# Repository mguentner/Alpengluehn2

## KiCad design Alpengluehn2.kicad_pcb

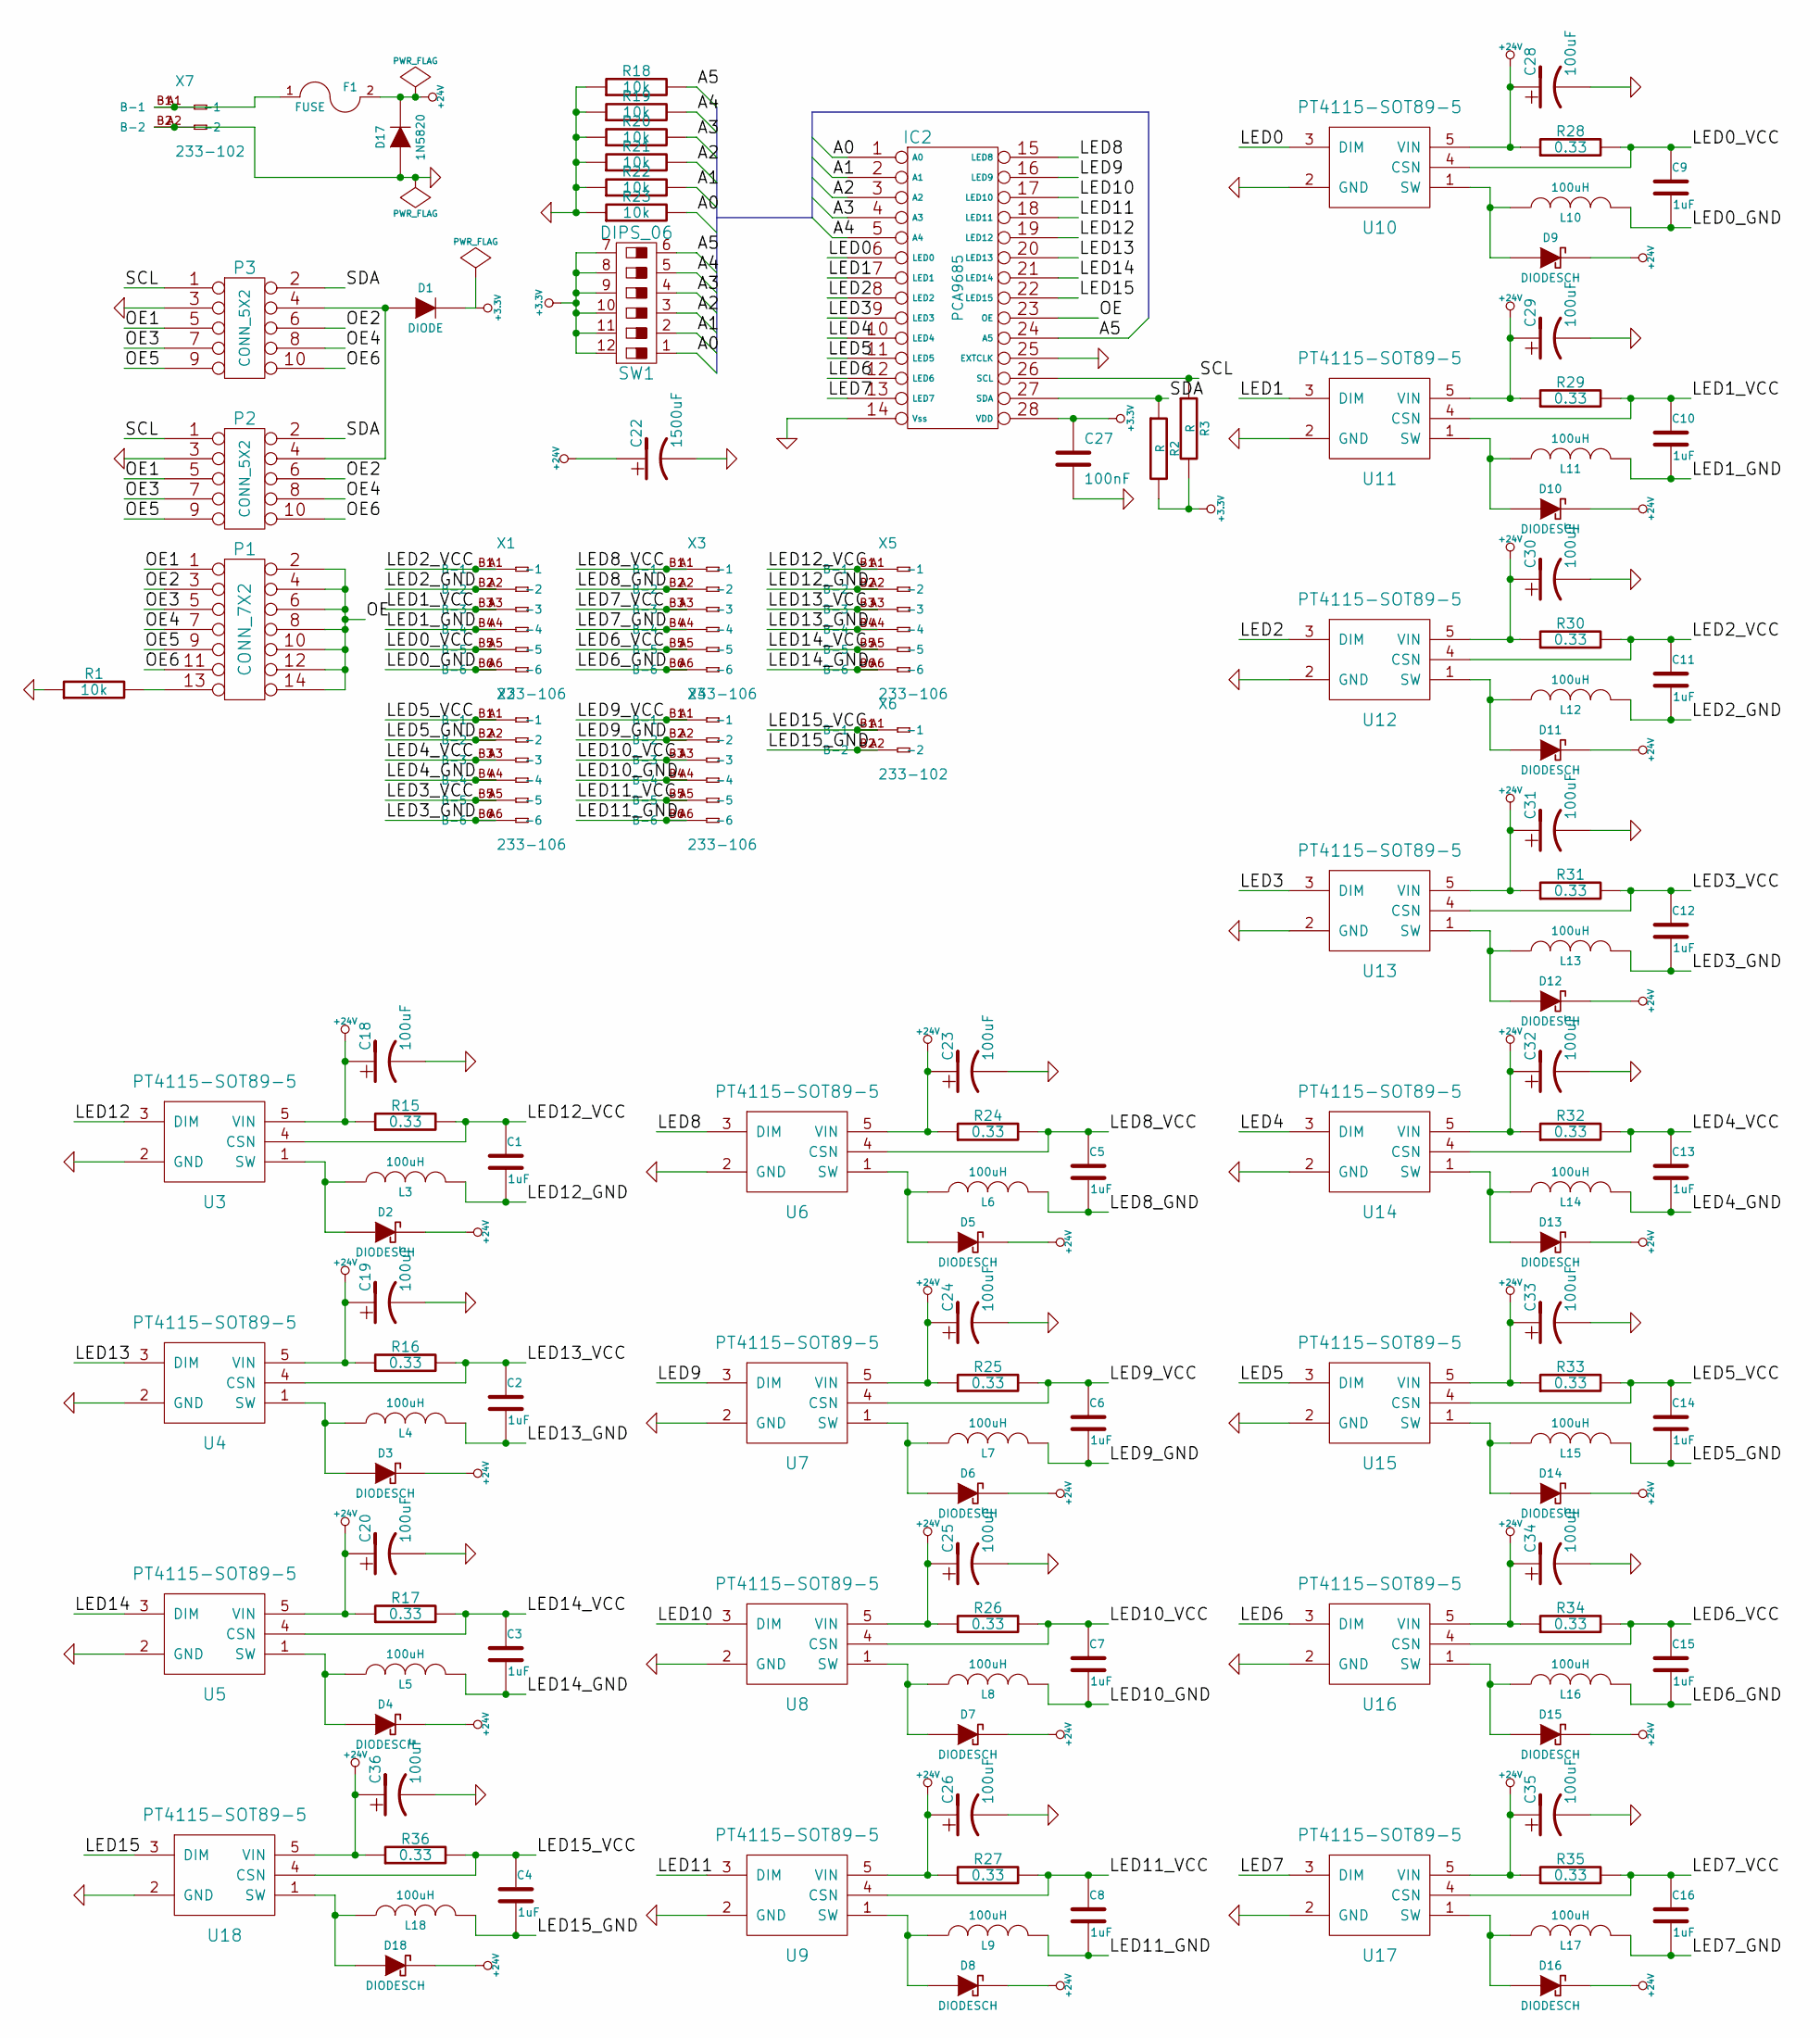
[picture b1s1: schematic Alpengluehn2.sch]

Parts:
C1, C2, C3, C4, C5, C6, C7, C8, C9, C10, C11, C12, C13, C14, C15, C16: 1uF
C18, C19, C20, C23, C24, C25, C26, C28, C29, C30, C31, C32, C33, C34, C35, C36: 100uF
C22: 1500uF
C27: 100nF
D1: DIODE
D2, D3, D4, D5, D6, D7, D8, D9, D10, D11, D12, D13, D14, D15, D16, D18: DIODESCH
D17: 1N5820
F1: FUSE
IC2: PCA9685
L3, L4, L5, L6, L7, L8, L9, L10, L11, L12, L13, L14, L15, L16, L17, L18: 100uH
P1: CONN_7X2
P2, P3: CONN_5X2
R1, R18, R19, R20, R21, R22, R23: 10k
R2, R3: R
R15, R16, R17, R24, R25, R26, R27, R28, R29, R30, R31, R32, R33, R34, R35, R36: 0.33
SW1: DIPS_06
U3, U4, U5, U6, U7, U8, U9, U10, U11, U12, U13, U14, U15, U16, U17, U18: PT4115-SOT89-5
X1, X2, X3, X4, X5: 233-106; con-wago-233-106
X6, X7: 233-102; con-wago-233-102

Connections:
+3.3V: C27.1, D1.2 (K), IC2.28 (VDD), R2.2, R3.2, SW1.7, SW1.8, SW1.9, SW1.10, SW1.11, SW1.12
+24V: C18.1, C19.1, C20.1, C22.1, C23.1, C24.1, C25.1, C26.1, C28.1, C29.1, C30.1, C31.1, C32.1, C33.1, C34.1, C35.1, C36.1, D2.2 (K), D3.2 (K), D4.2 (K), D5.2 (K), D6.2 (K), D7.2 (K), D8.2 (K), D9.2 (K), D10.2 (K), D11.2 (K), D12.2 (K), D13.2 (K), D14.2 (K), D15.2 (K), D16.2 (K), D17.2 (K), D18.2 (K), F1.2, R15.1, R16.1, R17.1, R24.1, R25.1, R26.1, R27.1, R28.1, R29.1, R30.1, R31.1, R32.1, R33.1, R34.1, R35.1, R36.1, U3.5 (VIN), U4.5 (VIN), U5.5 (VIN), U6.5 (VIN), U7.5 (VIN), U8.5 (VIN), U9.5 (VIN), U10.5 (VIN), U11.5 (VIN), U12.5 (VIN), U13.5 (VIN), U14.5 (VIN), U15.5 (VIN), U16.5 (VIN), U17.5 (VIN), U18.5 (VIN)
/A0: IC2.1 (A0), R23.2, SW1.1
/A1: IC2.2 (A1), R22.2, SW1.2
/A2: IC2.3 (A2), R21.2, SW1.3
/A3: IC2.4 (A3), R20.2, SW1.4
/A4: IC2.5 (A4), R19.2, SW1.5
/A5: IC2.24 (A5), R18.2, SW1.6
/LED0: IC2.6 (LED0), U10.3 (DIM)
/LED0_GND: C9.2, L10.2, X1.A6 (-6), X1.B6 (B-6)
/LED0_VCC: C9.1, R28.2, U10.4 (CSN), X1.A5 (-5), X1.B5 (B-5)
/LED1: IC2.7 (LED1), U11.3 (DIM)
/LED1_GND: C10.2, L11.2, X1.A4 (-4), X1.B4 (B-4)
/LED1_VCC: C10.1, R29.2, U11.4 (CSN), X1.A3 (-3), X1.B3 (B-3)
/LED2: IC2.8 (LED2), U12.3 (DIM)
/LED2_GND: C11.2, L12.2, X1.A2 (-2), X1.B2 (B-2)
/LED2_VCC: C11.1, R30.2, U12.4 (CSN), X1.A1 (-1), X1.B1 (B-1)
/LED3: IC2.9 (LED3), U13.3 (DIM)
/LED3_GND: C12.2, L13.2, X2.A6 (-6), X2.B6 (B-6)
/LED3_VCC: C12.1, R31.2, U13.4 (CSN), X2.A5 (-5), X2.B5 (B-5)
/LED4: IC2.10 (LED4), U14.3 (DIM)
/LED4_GND: C13.2, L14.2, X2.A4 (-4), X2.B4 (B-4)
/LED4_VCC: C13.1, R32.2, U14.4 (CSN), X2.A3 (-3), X2.B3 (B-3)
/LED5: IC2.11 (LED5), U15.3 (DIM)
/LED5_GND: C14.2, L15.2, X2.A2 (-2), X2.B2 (B-2)
/LED5_VCC: C14.1, R33.2, U15.4 (CSN), X2.A1 (-1), X2.B1 (B-1)
/LED6: IC2.12 (LED6), U16.3 (DIM)
/LED6_GND: C15.2, L16.2, X3.A6 (-6), X3.B6 (B-6)
/LED6_VCC: C15.1, R34.2, U16.4 (CSN), X3.A5 (-5), X3.B5 (B-5)
/LED7: IC2.13 (LED7), U17.3 (DIM)
/LED7_GND: C16.2, L17.2, X3.A4 (-4), X3.B4 (B-4)
/LED7_VCC: C16.1, R35.2, U17.4 (CSN), X3.A3 (-3), X3.B3 (B-3)
/LED8: IC2.15 (LED8), U6.3 (DIM)
/LED8_GND: C5.2, L6.2, X3.A2 (-2), X3.B2 (B-2)
/LED8_VCC: C5.1, R24.2, U6.4 (CSN), X3.A1 (-1), X3.B1 (B-1)
/LED9: IC2.16 (LED9), U7.3 (DIM)
/LED9_GND: C6.2, L7.2, X4.A2 (-2), X4.B2 (B-2)
/LED9_VCC: C6.1, R25.2, U7.4 (CSN), X4.A1 (-1), X4.B1 (B-1)
/LED10: IC2.17 (LED10), U8.3 (DIM)
/LED10_GND: C7.2, L8.2, X4.A4 (-4), X4.B4 (B-4)
/LED10_VCC: C7.1, R26.2, U8.4 (CSN), X4.A3 (-3), X4.B3 (B-3)
/LED11: IC2.18 (LED11), U9.3 (DIM)
/LED11_GND: C8.2, L9.2, X4.A6 (-6), X4.B6 (B-6)
/LED11_VCC: C8.1, R27.2, U9.4 (CSN), X4.A5 (-5), X4.B5 (B-5)
/LED12: IC2.19 (LED12), U3.3 (DIM)
/LED12_GND: C1.2, L3.2, X5.A2 (-2), X5.B2 (B-2)
/LED12_VCC: C1.1, R15.2, U3.4 (CSN), X5.A1 (-1), X5.B1 (B-1)
/LED13: IC2.20 (LED13), U4.3 (DIM)
/LED13_GND: C2.2, L4.2, X5.A4 (-4), X5.B4 (B-4)
/LED13_VCC: C2.1, R16.2, U4.4 (CSN), X5.A3 (-3), X5.B3 (B-3)
/LED14: IC2.21 (LED14), U5.3 (DIM)
/LED14_GND: C3.2, L5.2, X5.A6 (-6), X5.B6 (B-6)
/LED14_VCC: C3.1, R17.2, U5.4 (CSN), X5.A5 (-5), X5.B5 (B-5)
/LED15: IC2.22 (LED15), U18.3 (DIM)
/LED15_GND: C4.2, L18.2, X6.A2 (-2), X6.B2 (B-2)
/LED15_VCC: C4.1, R36.2, U18.4 (CSN), X6.A1 (-1), X6.B1 (B-1)
/OE: IC2.23 (OE), P1.2, P1.4, P1.6, P1.8, P1.10, P1.12, P1.14
/OE1: P1.1, P2.5, P3.5
/OE2: P1.3, P2.6, P3.6
/OE3: P1.5, P2.7, P3.7
/OE4: P1.7, P2.8, P3.8
/OE5: P1.9, P2.9, P3.9
/OE6: P1.11, P2.10, P3.10
/SCL: IC2.26 (SCL), P2.1, P3.1, R3.1
/SDA: IC2.27 (SDA), P2.2, P3.2, R2.1
GND: C18.2, C19.2, C20.2, C22.2, C23.2, C24.2, C25.2, C26.2, C27.2, C28.2, C29.2, C30.2, C31.2, C32.2, C33.2, C34.2, C35.2, C36.2, D17.1 (A), IC2.14 (Vss), IC2.25 (EXTCLK), P2.3, P3.3, R1.1, R18.1, R19.1, R20.1, R21.1, R22.1, R23.1, U3.2 (GND), U4.2 (GND), U5.2 (GND), U6.2 (GND), U7.2 (GND), U8.2 (GND), U9.2 (GND), U10.2 (GND), U11.2 (GND), U12.2 (GND), U13.2 (GND), U14.2 (GND), U15.2 (GND), U16.2 (GND), U17.2 (GND), U18.2 (GND), X7.A2 (-2), X7.B2 (B-2)
unnamed: D13.1 (A), L14.1, U14.1 (SW)
unnamed: D14.1 (A), L15.1, U15.1 (SW)
unnamed: D6.1 (A), L7.1, U7.1 (SW)
unnamed: D5.1 (A), L6.1, U6.1 (SW)
unnamed: D12.1 (A), L13.1, U13.1 (SW)
unnamed: D11.1 (A), L12.1, U12.1 (SW)
unnamed: D16.1 (A), L17.1, U17.1 (SW)
unnamed: D15.1 (A), L16.1, U16.1 (SW)
unnamed: D18.1 (A), L18.1, U18.1 (SW)
unnamed: D1.1 (A), P2.4, P3.4
unnamed: P1.13, R1.2
unnamed: D2.1 (A), L3.1, U3.1 (SW)
unnamed: F1.1, X7.A1 (-1), X7.B1 (B-1)
unnamed: D8.1 (A), L9.1, U9.1 (SW)
unnamed: D7.1 (A), L8.1, U8.1 (SW)
unnamed: D3.1 (A), L4.1, U4.1 (SW)
unnamed: D4.1 (A), L5.1, U5.1 (SW)
unnamed: D9.1 (A), L10.1, U10.1 (SW)
unnamed: D10.1 (A), L11.1, U11.1 (SW)

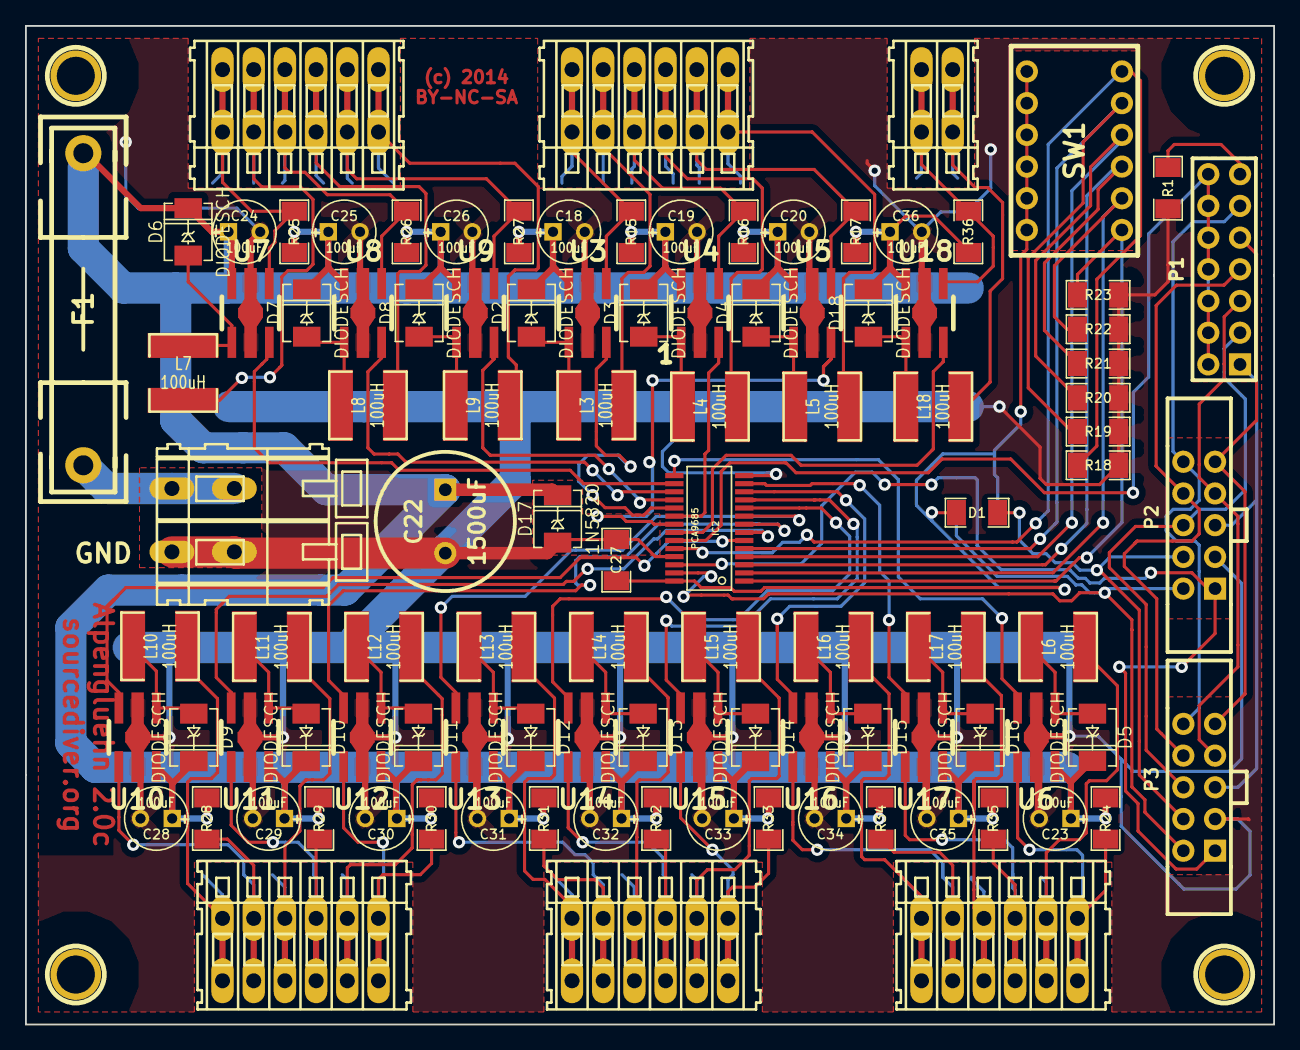
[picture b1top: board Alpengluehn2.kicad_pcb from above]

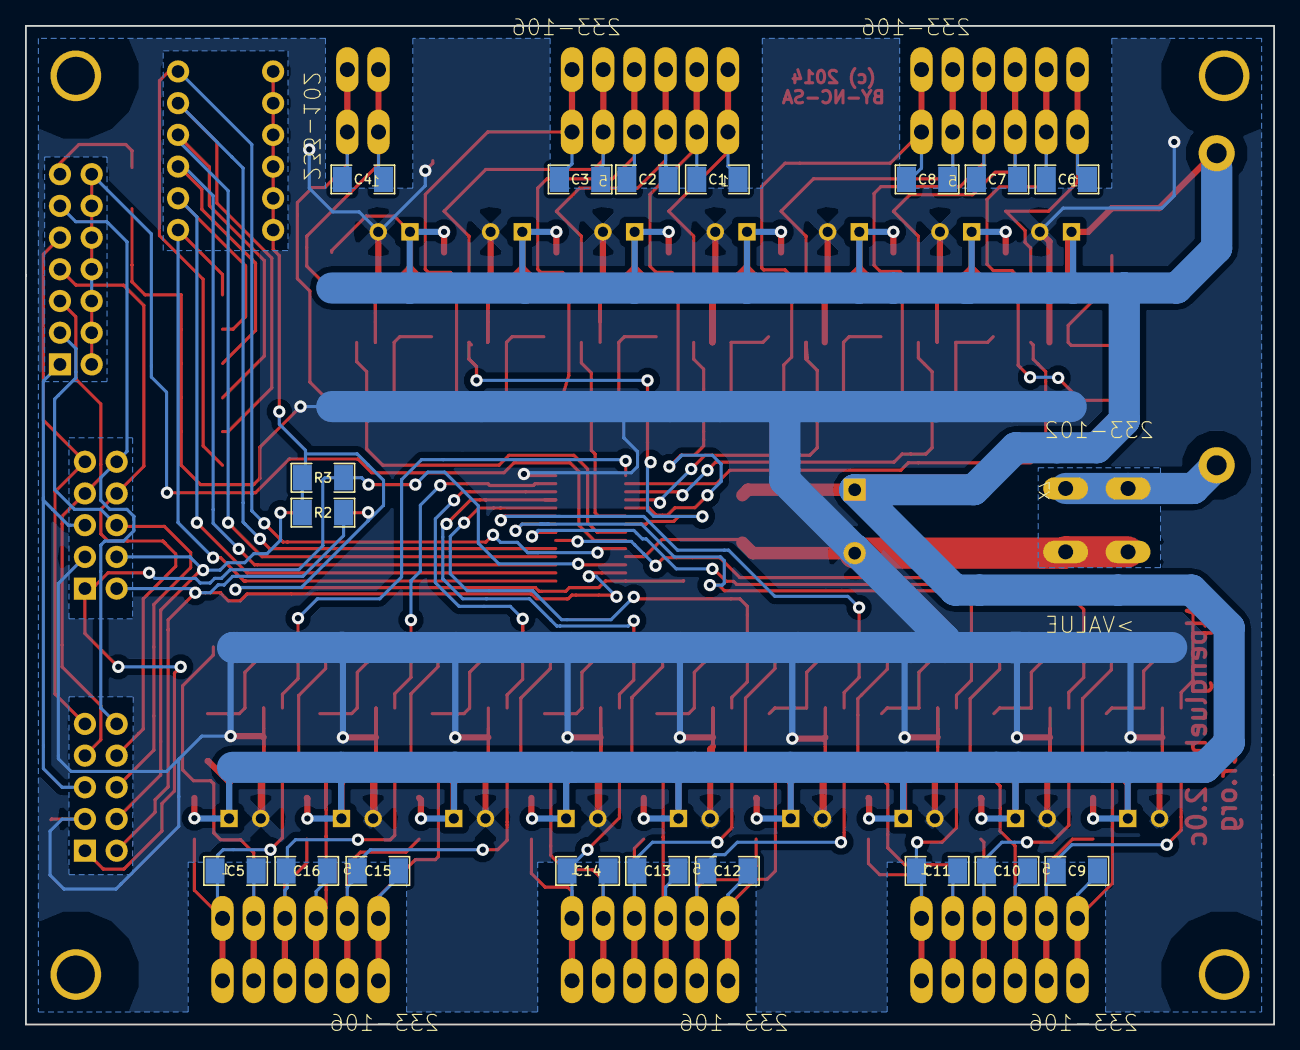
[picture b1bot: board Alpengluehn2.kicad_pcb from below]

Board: 2 copper layers, 100.0 x 80.0 mm, 126 parts (18 on the bottom side), 85 nets.

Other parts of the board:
1PIN, 1PIN#2, 1PIN#3, 1PIN#4: P***; 1pin

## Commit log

2014-05-02 changed inductor footprint and overall layout
    + Version is now 2.0c
    + added 1uF buffers to LED+ and LED GND
2014-05-02 made some drawings invisible, added gerber files
2014-10-28 corrected drawing of power connector

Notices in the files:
Alpengluehn2.kicad_pcb:
(c) 2014
